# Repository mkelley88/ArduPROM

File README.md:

ArduPROM
========

An (E)EPROM shield designed for reading and writing from the Arduino UNO. Currently it should work with any chip that is pin compatable with the 27C512. 

I have designed this simple board and software to pull the contents of an EPROM or EEPROM chip over the USB serial line of the Ardunio UNO. I am currently using CoolTerm with the option of saving incoming data as a txt file. This seems to be a solution for now. If anyone out there would like to support this project and design a quick OSX, Linux, or Windows software to bring in the data and save it, that would be greatly helpful!

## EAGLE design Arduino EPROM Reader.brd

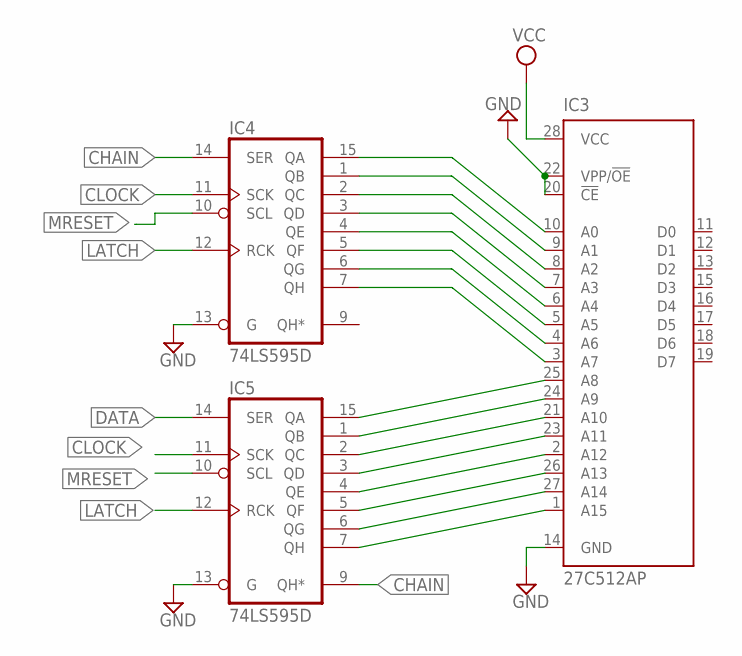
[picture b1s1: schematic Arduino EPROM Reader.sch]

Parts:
IC3: 27C512AP; DIL28-6
IC4, IC5: 74LS595D; SO16

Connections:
CHAIN: IC4.14 (SER), IC5.9 (QH*)
CLOCK: IC4.11 (SCK), IC5.11 (SCK)
DATA: IC5.14 (SER)
GND: IC3.14 (GND), IC3.20 (!CE), IC3.22 (VPP/!OE), IC4.8 (GND), IC4.13 (G), IC5.8 (GND), IC5.13 (G)
LATCH: IC4.12 (RCK), IC5.12 (RCK)
MRESET: IC4.10 (SCL), IC5.10 (SCL)
unnamed: IC3.10 (A0), IC4.15 (QA)
unnamed: IC3.9 (A1), IC4.1 (QB)
unnamed: IC3.8 (A2), IC4.2 (QC)
unnamed: IC3.7 (A3), IC4.3 (QD)
unnamed: IC3.6 (A4), IC4.4 (QE)
unnamed: IC3.5 (A5), IC4.5 (QF)
unnamed: IC3.4 (A6), IC4.6 (QG)
unnamed: IC3.3 (A7), IC4.7 (QH)
unnamed: IC3.25 (A8), IC5.15 (QA)
unnamed: IC3.24 (A9), IC5.1 (QB)
unnamed: IC3.21 (A10), IC5.2 (QC)
unnamed: IC3.23 (A11), IC5.3 (QD)
unnamed: IC3.2 (A12), IC5.4 (QE)
unnamed: IC3.26 (A13), IC5.5 (QF)
unnamed: IC3.27 (A14), IC5.6 (QG)
unnamed: IC3.1 (A15), IC5.7 (QH)
VCC: IC3.28 (VCC), IC4.16 (VCC), IC5.16 (VCC)

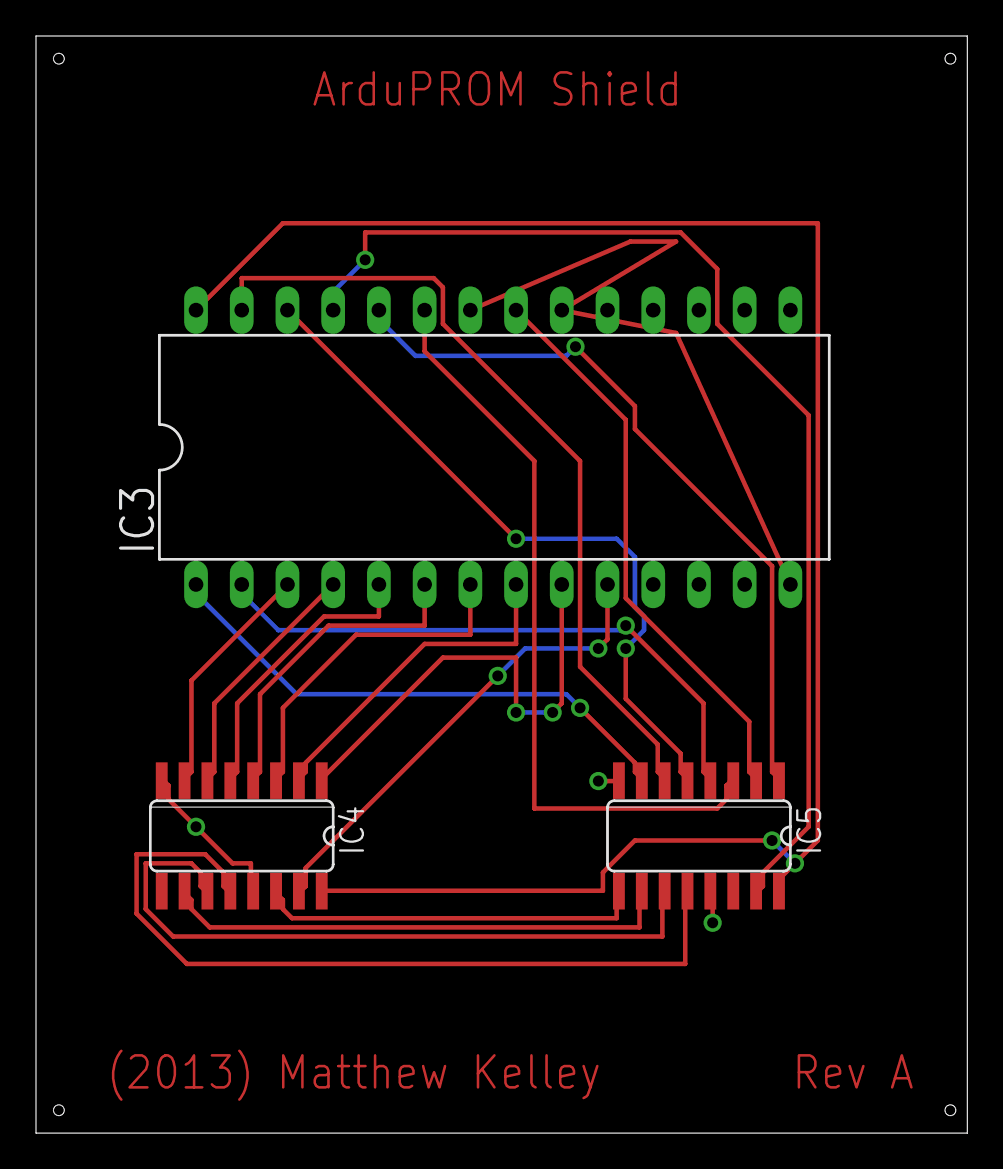
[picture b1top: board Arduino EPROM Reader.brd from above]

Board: 2 copper layers, 51.7 x 61.0 mm, 3 parts (0 on the bottom side), 22 nets.

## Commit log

2013-09-29 Inital Upload
    ArduPROM Firmware v0.7
    Eagle Board and Schematic
